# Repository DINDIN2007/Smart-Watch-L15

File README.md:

# Smart-Watch-L15
This is a demo board to showcase development with both the BlystL15 (based on the nrf54L15) and the IOComposer AI from I-Syst.inc.

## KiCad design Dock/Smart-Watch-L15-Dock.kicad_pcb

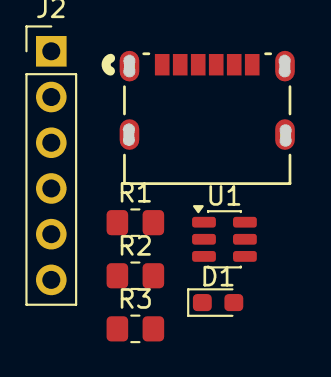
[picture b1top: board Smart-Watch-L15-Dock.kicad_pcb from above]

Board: 2 copper layers, 7 parts (0 on the bottom side), 9 nets, no tracks yet.

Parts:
D1: LED; LED_0603_1608Metric_Pad1.05x0.95mm_HandSolder
J1: USB4125-GF-A; CONN6_USB4125_GCT
J2: Conn_01x06; PinHeader_1x06_P2.54mm_Vertical
R1, R2: 5.1k; R_0805_2012Metric_Pad1.20x1.40mm_HandSolder
R3: 2.2k; R_0805_2012Metric_Pad1.20x1.40mm_HandSolder
U1: USBLC6-4SC6; SOT-23-6

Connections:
+5V: J1.A9 (VBUS), J1.B9 (VBUS), J2.1, R3.2, U1.5 (VBUS)
/SWDCLK: J2.4, U1.4 (I/O3)
/SWDIO: J2.3, U1.6 (I/O4)
/nRESET: J2.5, U1.3 (I/O2)
GND: D1.1 (K), J1.A12 (GND), J1.B12 (GND), J2.2, R1.2, R2.2, U1.2 (GND)
unnamed: D1.2 (A), R3.1
unnamed: J1.A5 (CC1), R1.1
unnamed: J1.B5 (CC2), R2.1
VDD: J2.6, U1.1 (I/O1)

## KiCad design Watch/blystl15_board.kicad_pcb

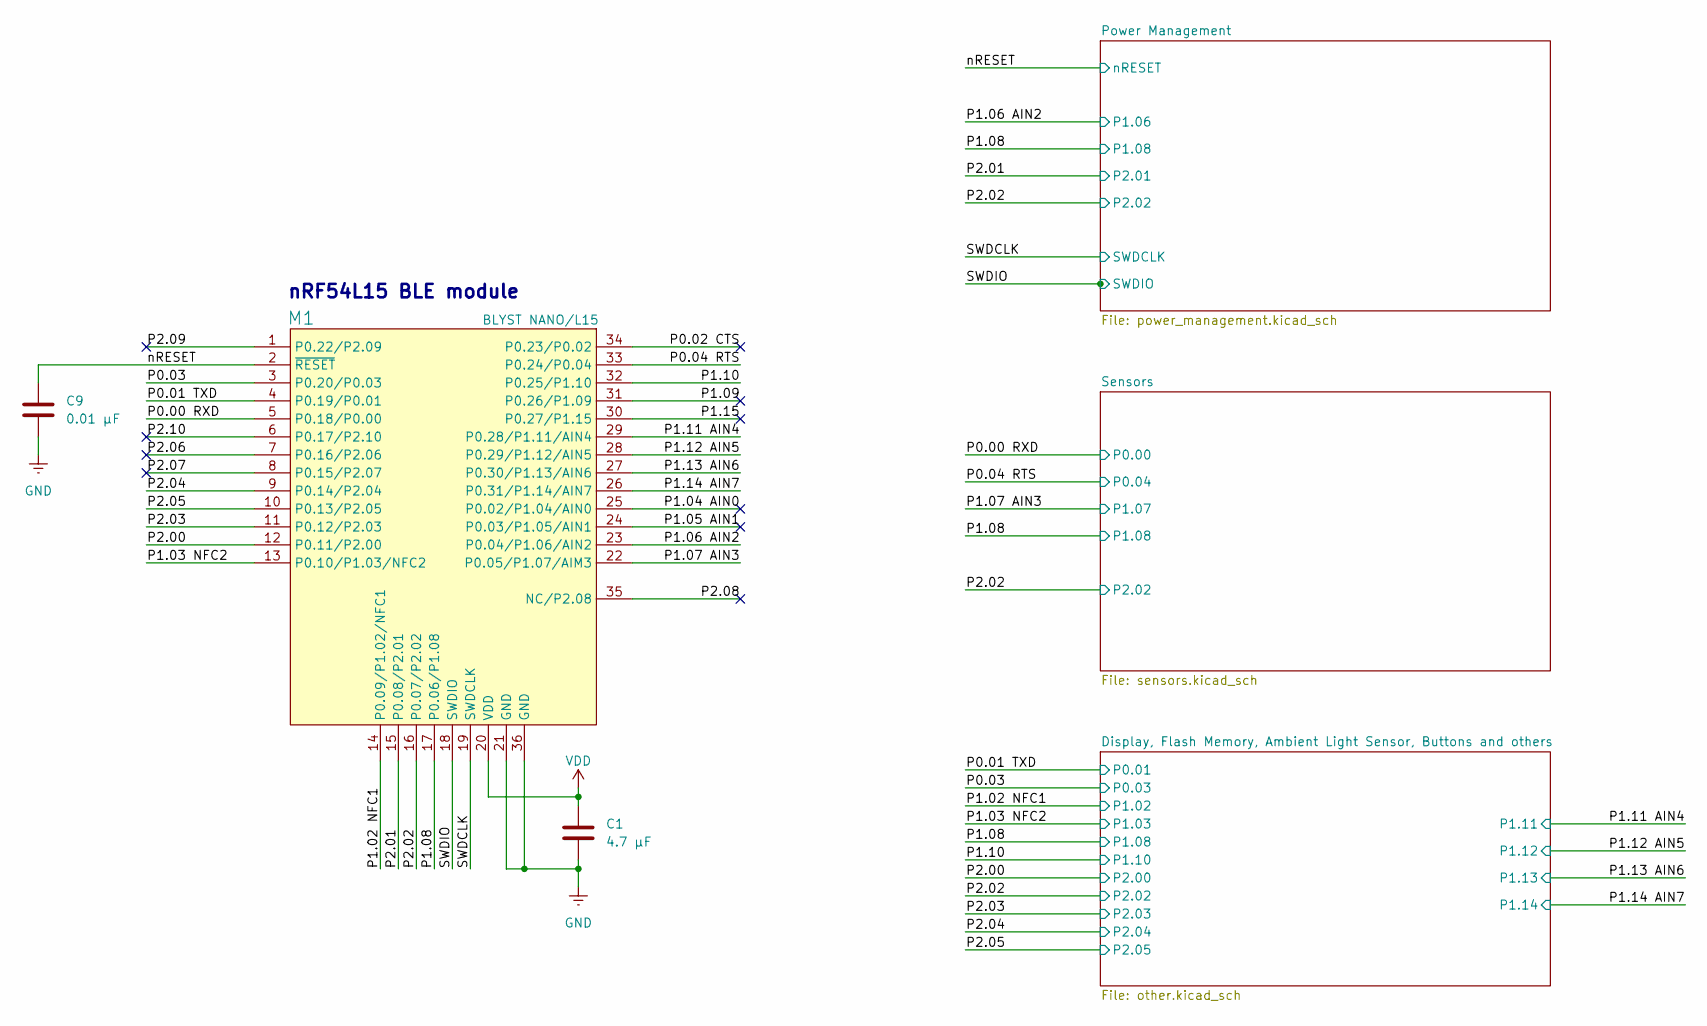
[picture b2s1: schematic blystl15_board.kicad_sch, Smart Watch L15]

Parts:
C1: 4.7 μF; C_0603_1608Metric
C9: 0.01 μF; C_0402_1005Metric
M1: BLYST NANO/L15; BLYSTL15

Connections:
/P0.00 RXD: M1.5 (P0.18/P0.00); also elsewhere on the board
/P0.01 TXD: M1.4 (P0.19/P0.01); also elsewhere on the board
/P0.02 CTS: M1.34 (P0.23/P0.02)
/P0.03: M1.3 (P0.20/P0.03); also elsewhere on the board
/P0.04 RTS: M1.33 (P0.24/P0.04); also elsewhere on the board
/P1.02 NFC1: M1.14 (P0.09/P1.02/NFC1); also elsewhere on the board
/P1.03 NFC2: M1.13 (P0.10/P1.03/NFC2); also elsewhere on the board
/P1.04 AIN0: M1.25 (P0.02/P1.04/AIN0)
/P1.05 AIN1: M1.24 (P0.03/P1.05/AIN1)
/P1.06 AIN2: M1.23 (P0.04/P1.06/AIN2); also elsewhere on the board
/P1.07 AIN3: M1.22 (P0.05/P1.07/AIM3); also elsewhere on the board
/P1.08: M1.17 (P0.06/P1.08); also elsewhere on the board
/P1.09: M1.31 (P0.26/P1.09)
/P1.10: M1.32 (P0.25/P1.10); also elsewhere on the board
/P1.11 AIN4: M1.29 (P0.28/P1.11/AIN4); also elsewhere on the board
/P1.12 AIN5: M1.28 (P0.29/P1.12/AIN5); also elsewhere on the board
/P1.13 AIN6: M1.27 (P0.30/P1.13/AIN6); also elsewhere on the board
/P1.14 AIN7: M1.26 (P0.31/P1.14/AIN7); also elsewhere on the board
/P1.15: M1.30 (P0.27/P1.15)
/P2.00: M1.12 (P0.11/P2.00); also elsewhere on the board
/P2.01: M1.15 (P0.08/P2.01); also elsewhere on the board
/P2.02: M1.16 (P0.07/P2.02); also elsewhere on the board
/P2.03: M1.11 (P0.12/P2.03); also elsewhere on the board
/P2.04: M1.9 (P0.14/P2.04); also elsewhere on the board
/P2.05: M1.10 (P0.13/P2.05); also elsewhere on the board
/P2.06: M1.7 (P0.16/P2.06)
/P2.07: M1.8 (P0.15/P2.07)
/P2.08: M1.35 (NC/P2.08)
/P2.09: M1.1 (P0.22/P2.09)
/P2.10: M1.6 (P0.17/P2.10)
/SWDCLK: M1.19 (SWDCLK); also elsewhere on the board
/SWDIO: M1.18 (SWDIO); also elsewhere on the board
/nRESET: C9.1, M1.2 (~RESET); also elsewhere on the board
GND: C1.2, C9.2, M1.21 (GND), M1.36 (GND); also elsewhere on the board
VDD: C1.1, M1.20 (VDD); also elsewhere on the board

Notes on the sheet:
nRF54L15 BLE module

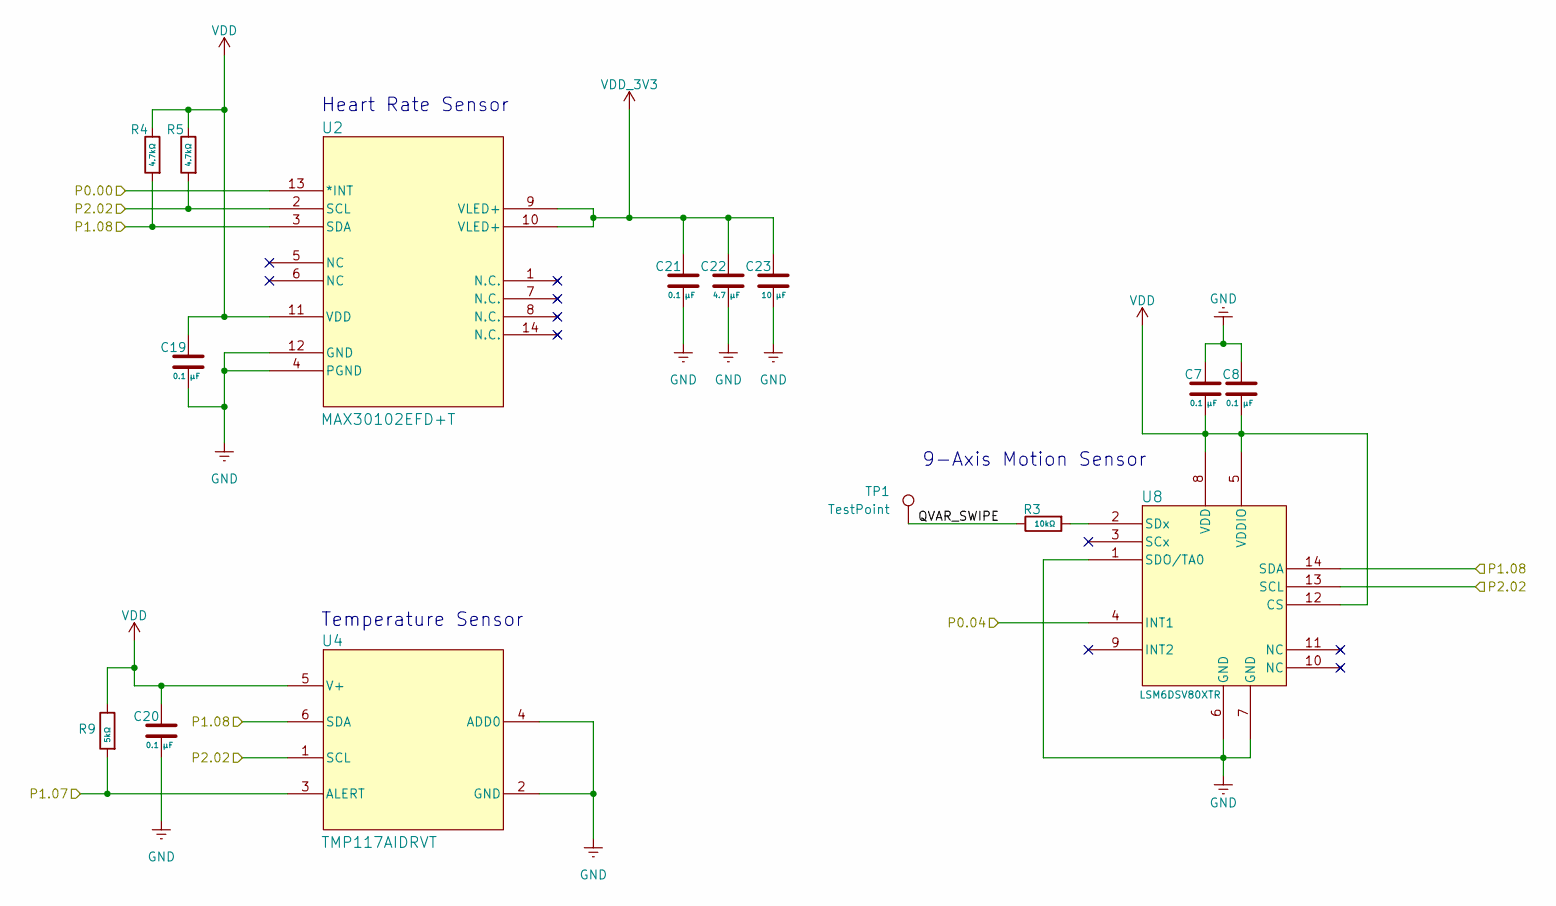
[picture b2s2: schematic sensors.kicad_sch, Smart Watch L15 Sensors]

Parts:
C7, C8, C19, C20, C21: 0.1 μF; C_0402_1005Metric
C22: 4.7 μF; C_0402_1005Metric
C23: 10 μF; C_0402_1005Metric
R3: 10kΩ; R_0402_1005Metric
R4, R5: 4.7kΩ; R_0402_1005Metric
R9: 5kΩ; R_0402_1005Metric
TP1: TestPoint
U2: MAX30102EFD+T; 21-1048_F143A5&plus_1_MXM-L
U4: TMP117AIDRVT; DRV0006B
U8: LSM6DSV80XTR; QFN_LSM6DSV80XTR_STM-M

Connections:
/P0.00 RXD: U2.13 (*INT); also elsewhere on the board
/P0.04 RTS: U8.4 (INT1); also elsewhere on the board
/P1.07 AIN3: R9.2, U4.3 (ALERT); also elsewhere on the board
/P1.08: R4.2, U2.3 (SDA), U4.6 (SDA), U8.14 (SDA); also elsewhere on the board
/P2.02: R5.2, U2.2 (SCL), U4.1 (SCL), U8.13 (SCL); also elsewhere on the board
/Sensors/QVAR_SWIPE: R3.1, TP1.1
GND: C7.1, C8.1, C19.2, C20.2, C21.2, C22.2, C23.2, U2.4 (PGND), U2.12 (GND), U4.2 (GND), U4.4 (ADD0), U8.1 (SDO/TA0), U8.6 (GND), U8.7 (GND); also elsewhere on the board
unnamed: R3.2, U8.2 (SDx)
VDD: C7.2, C8.2, C19.1, C20.1, R4.1, R5.1, R9.1, U2.11 (VDD), U4.5 (V+), U8.5 (VDDIO), U8.8 (VDD), U8.12 (CS); also elsewhere on the board
VDD_3V3: C21.1, C22.1, C23.1, U2.9 (VLED+), U2.10 (VLED+); also elsewhere on the board

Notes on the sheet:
9-Axis Motion Sensor
Temperature Sensor
Heart Rate Sensor

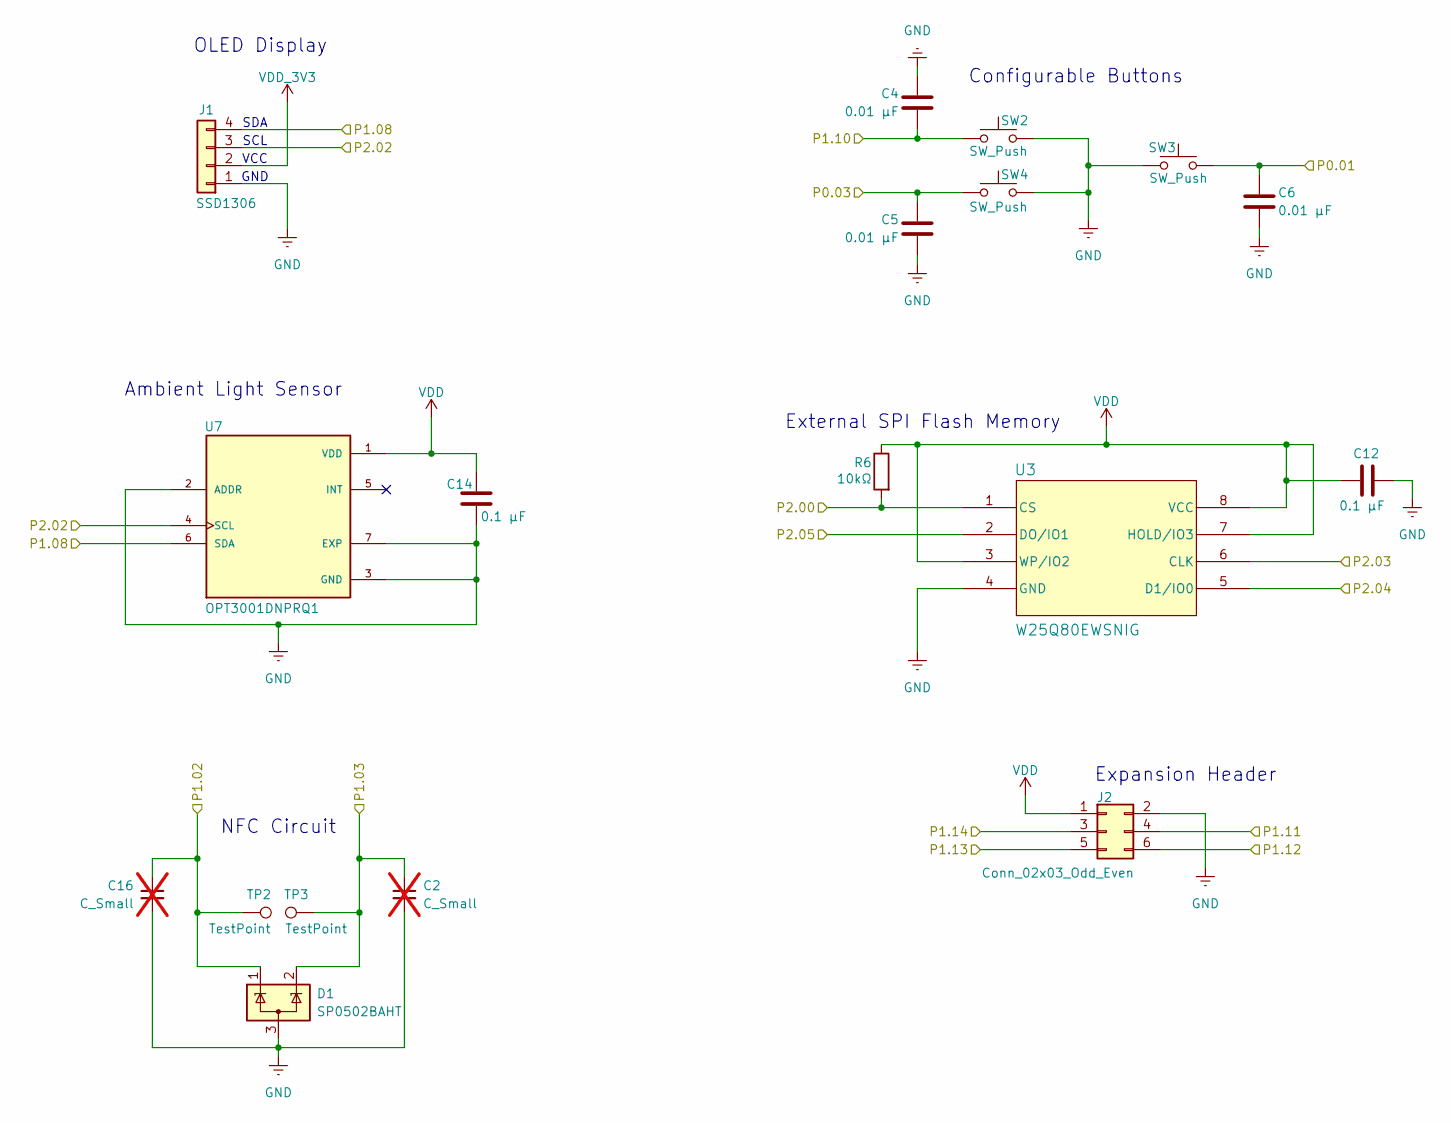
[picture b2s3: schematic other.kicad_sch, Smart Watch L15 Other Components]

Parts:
C2, C16: C_Small; C_0603_1608Metric_Pad1.08x0.95mm_HandSolder; not fitted
C4, C5, C6: 0.01 μF; C_0402_1005Metric
C12, C14: 0.1 μF; C_0402_1005Metric
D1: SP0502BAHT; SOT-23
J1: SSD1306; OLED_1.3in_I2C
J2: Conn_02x03_Odd_Even; PinHeader_2x03_P1.27mm_Vertical_SMD
R6: 10kΩ; R_0402_1005Metric
SW2, SW3, SW4: SW_Push; SW_Push_1P1T-MP_NO_Horizontal_Alps_SKRTLAE010
TP2, TP3: TestPoint; TestPoint_Pad_D1.0mm
U3: W25Q80EWSNIG; W25Q80EWSNIG_WIN-M
U7: OPT3001DNPRQ1; SON65P200X200X65-7N; PARTREV 01/2018

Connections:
/P0.01 TXD: C6.1, SW3.1; also elsewhere on the board
/P0.03: C5.1, SW4.1; also elsewhere on the board
/P1.02 NFC1: C16.1, D1.1 (K), TP2.1 (1_1); also elsewhere on the board
/P1.03 NFC2: C2.1, D1.2 (K), TP3.1 (1_1); also elsewhere on the board
/P1.08: J1.4, U7.6 (SDA); also elsewhere on the board
/P1.10: C4.2, SW2.1; also elsewhere on the board
/P1.11 AIN4: J2.4; also elsewhere on the board
/P1.12 AIN5: J2.6; also elsewhere on the board
/P1.13 AIN6: J2.5; also elsewhere on the board
/P1.14 AIN7: J2.3; also elsewhere on the board
/P2.00: R6.2, U3.1 (CS); also elsewhere on the board
/P2.02: J1.3, U7.4 (SCL); also elsewhere on the board
/P2.03: U3.6 (CLK); also elsewhere on the board
/P2.04: U3.5 (D1/IO0); also elsewhere on the board
/P2.05: U3.2 (DO/IO1); also elsewhere on the board
GND: C2.2, C4.1, C5.2, C6.2, C12.2, C14.2, C16.2, D1.3 (A), J1.1, J2.2, SW2.2, SW3.2, SW4.2, U3.4 (GND), U7.2 (ADDR), U7.3 (GND), U7.7 (EXP); also elsewhere on the board
VDD: C12.1, C14.1, J2.1, R6.1, U3.3 (WP/IO2), U3.7 (HOLD/IO3), U3.8 (VCC), U7.1 (VDD); also elsewhere on the board
VDD_3V3: J1.2; also elsewhere on the board

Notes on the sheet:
OLED Display
Expansion Header
SDA
Configurable Buttons
NFC Circuit
External SPI Flash Memory
SCL
Ambient Light Sensor
VCC
GND

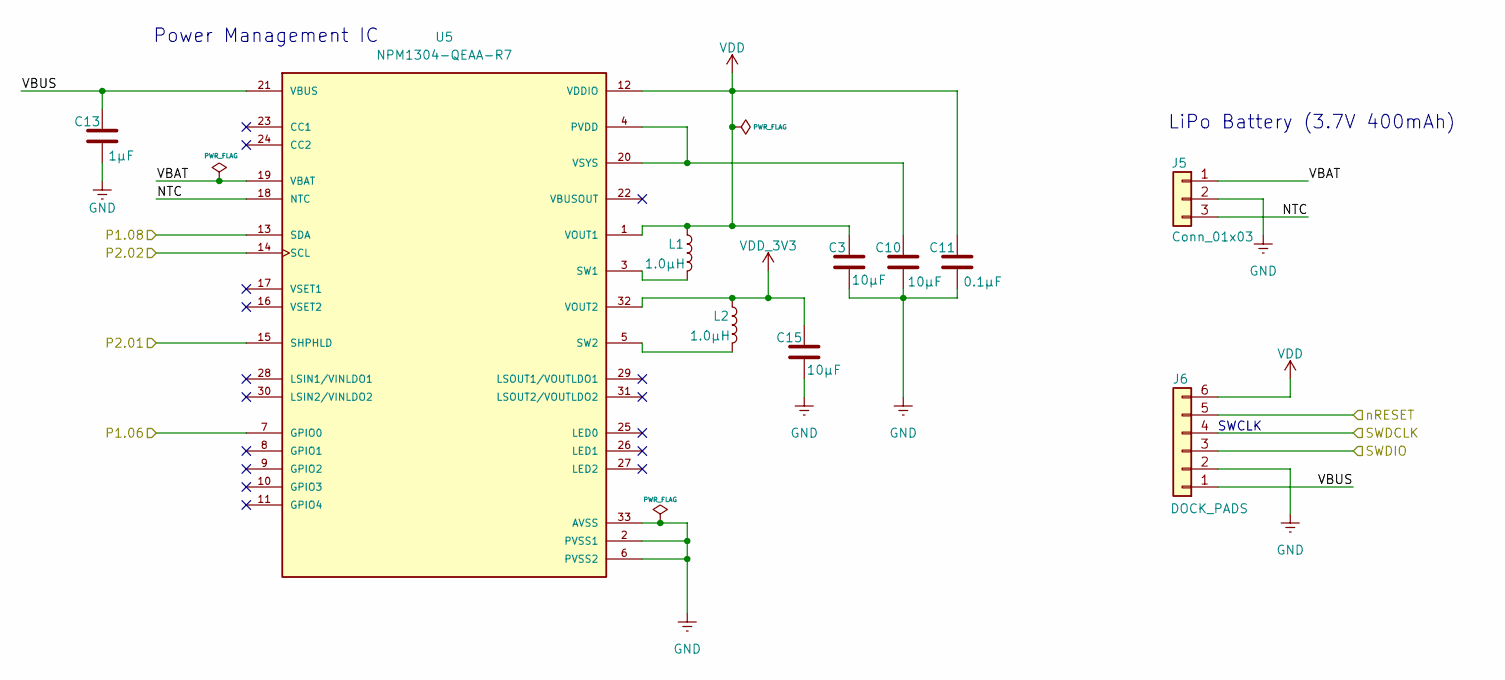
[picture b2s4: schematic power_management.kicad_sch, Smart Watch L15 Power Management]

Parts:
C3, C10, C15: 10µF; C_0603_1608Metric
C11: 0.1µF; C_0603_1608Metric
C13: 1µF; C_0603_1608Metric
J5: Conn_01x03; JST_PH_S3B-PH-SM4-TB_1x03-1MP_P2.00mm_Horizontal
J6: DOCK_PADS; Dock_Pads_6Pin
L1, L2: 1.0µH; L_0805_2012Metric
U5: NPM1304-QEAA-R7; QFN50P500X500X90-33N; PARTREV v1.1

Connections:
/P1.06 AIN2: U5.7 (GPIO0); also elsewhere on the board
/P1.08: U5.13 (SDA); also elsewhere on the board
/P2.01: U5.15 (SHPHLD); also elsewhere on the board
/P2.02: U5.14 (SCL); also elsewhere on the board
/Power Management/NTC: J5.3, U5.18 (NTC)
/Power Management/VBAT: J5.1, U5.19 (VBAT)
/Power Management/VBUS: C13.1, J6.1, U5.21 (VBUS)
/SWDCLK: J6.4; also elsewhere on the board
/SWDIO: J6.3; also elsewhere on the board
/nRESET: J6.5; also elsewhere on the board
GND: C3.2, C10.2, C11.2, C13.2, C15.2, J5.2, J6.2, U5.2 (PVSS1), U5.6 (PVSS2), U5.33 (AVSS); also elsewhere on the board
unnamed: C10.1, U5.4 (PVDD), U5.20 (VSYS)
unnamed: L1.2, U5.3 (SW1)
unnamed: L2.2, U5.5 (SW2)
VDD: C3.1, C11.1, J6.6, L1.1, U5.1 (VOUT1), U5.12 (VDDIO); also elsewhere on the board
VDD_3V3: C15.1, L2.1, U5.32 (VOUT2); also elsewhere on the board

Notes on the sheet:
Power Management IC
LiPo Battery (3.7V 400mAh)
SWCLK

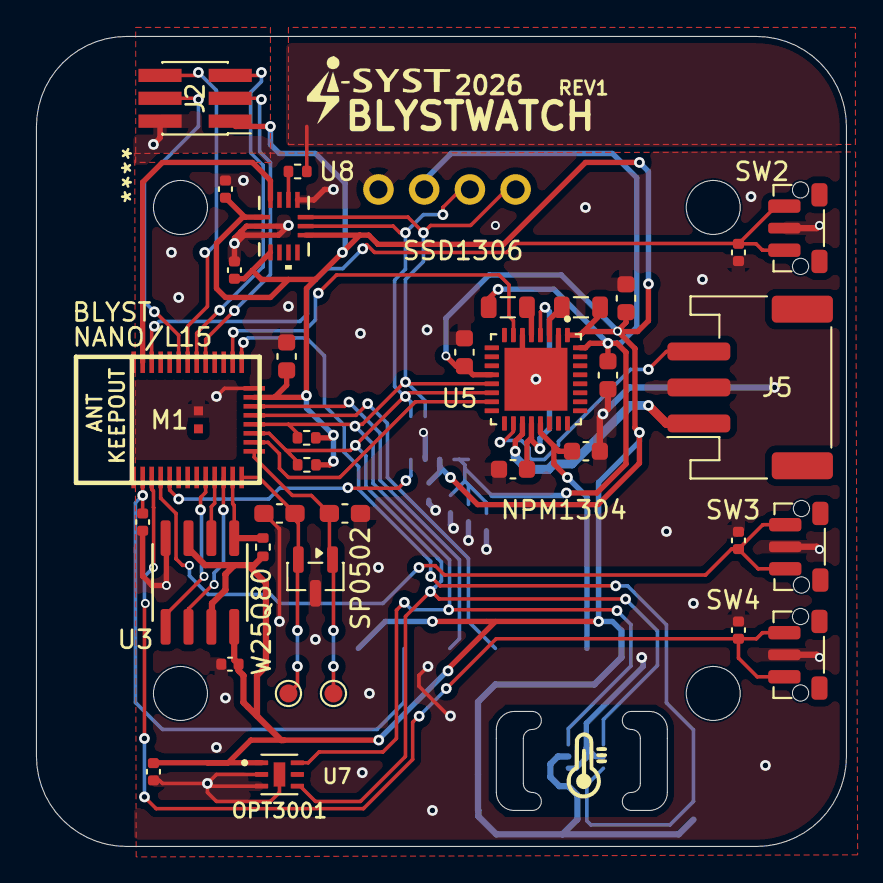
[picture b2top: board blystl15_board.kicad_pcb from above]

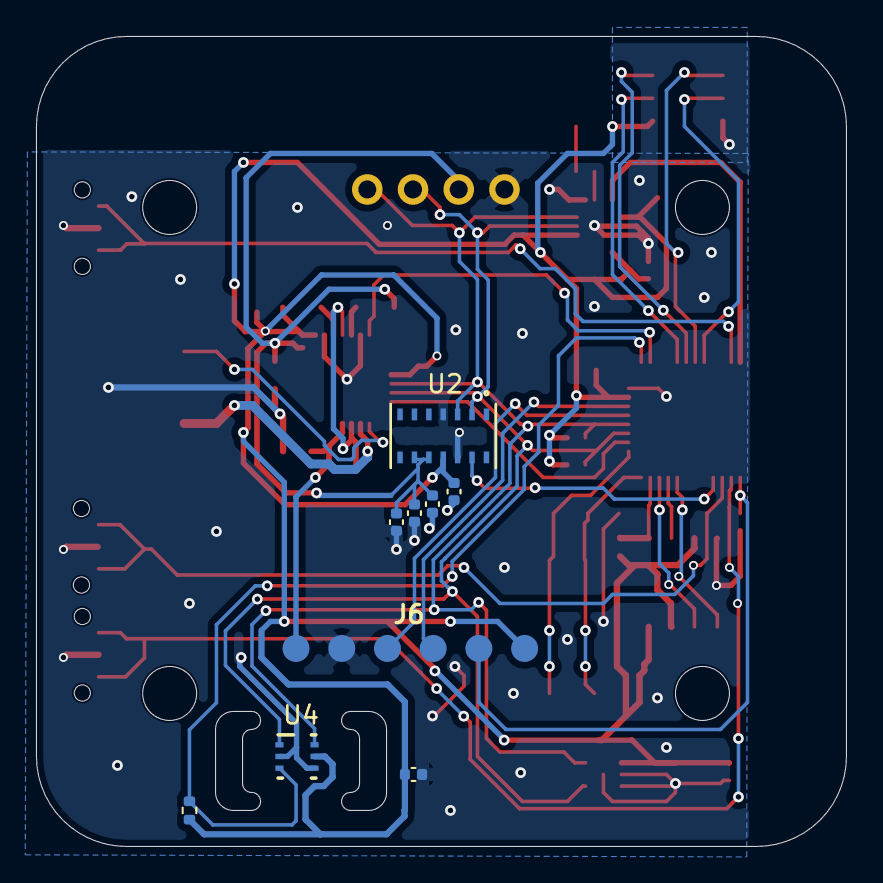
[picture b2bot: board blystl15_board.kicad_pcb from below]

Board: 2 copper layers, 45.0 x 45.0 mm, 45 parts (9 on the bottom side), 33 nets.

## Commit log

2026-03-13 Initial Commit with Basic Components imported in Schematic
2026-03-17 Schematic Draft
2026-03-18 All footprints imported in PCB editor
2026-03-18 Created custom footprints to match dimension of external boards
2026-03-20 Reorganization into multiple sheet and addition of BMP384, W25Q80DVSSIG and OPT3001DNPRQ1
2026-03-25 New Symbol for BlystL15
2026-03-26 Organized components in pcb layout editor
2026-03-27 PCB traces started
2026-03-27 Wired PMCI, dock pads, Hear Rate Sensor and 9-axis motion sensor
2026-05-01 Full Redesign of the Watch PCB (DRC still not fully passed)
2026-05-01 DRC Errors Cleared
2026-05-01 Move git root up one level to include Dock and Watch folders
2026-05-01 Schematic for Dock Done
